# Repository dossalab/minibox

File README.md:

## Minibox

This is a small Bluetooth receiver for remote controlled toys or small models. Receiver has 5 hobby servo / ESC outputs.
Since Xbox One's controller is essentially a Bluetooth gamepad, it is possible to bridge two together, turning them into a complete remote control solution.

### Connection

Switch your receiver and gamepad on. The LED on the receiver should start blinking quickly, indicating that it is in scanning mode. Once it will discover the controller it will start connecting automatically. If the connection is successful LED will turn off - then you're ready to go!

### Some considerations

- Range & reliability is probably not that great. It should be alright for cars and other ground vehicles but flying a drone like that could be dangerous (although I did);
- In case of inactivity (user is not interacting with the controller / not moving sticks), servos have to be reset to their initial position. That's because Xbox controller is designed for gaming, not for remote control. Once you stop moving sticks, controller enters low-power mode and stops sending data. Same happens when your model gets out of reach. It is hard for the receiver to distinguish these scenarios, so it has to disarm outputs in both cases (otherwise your model is at risk of running away :)

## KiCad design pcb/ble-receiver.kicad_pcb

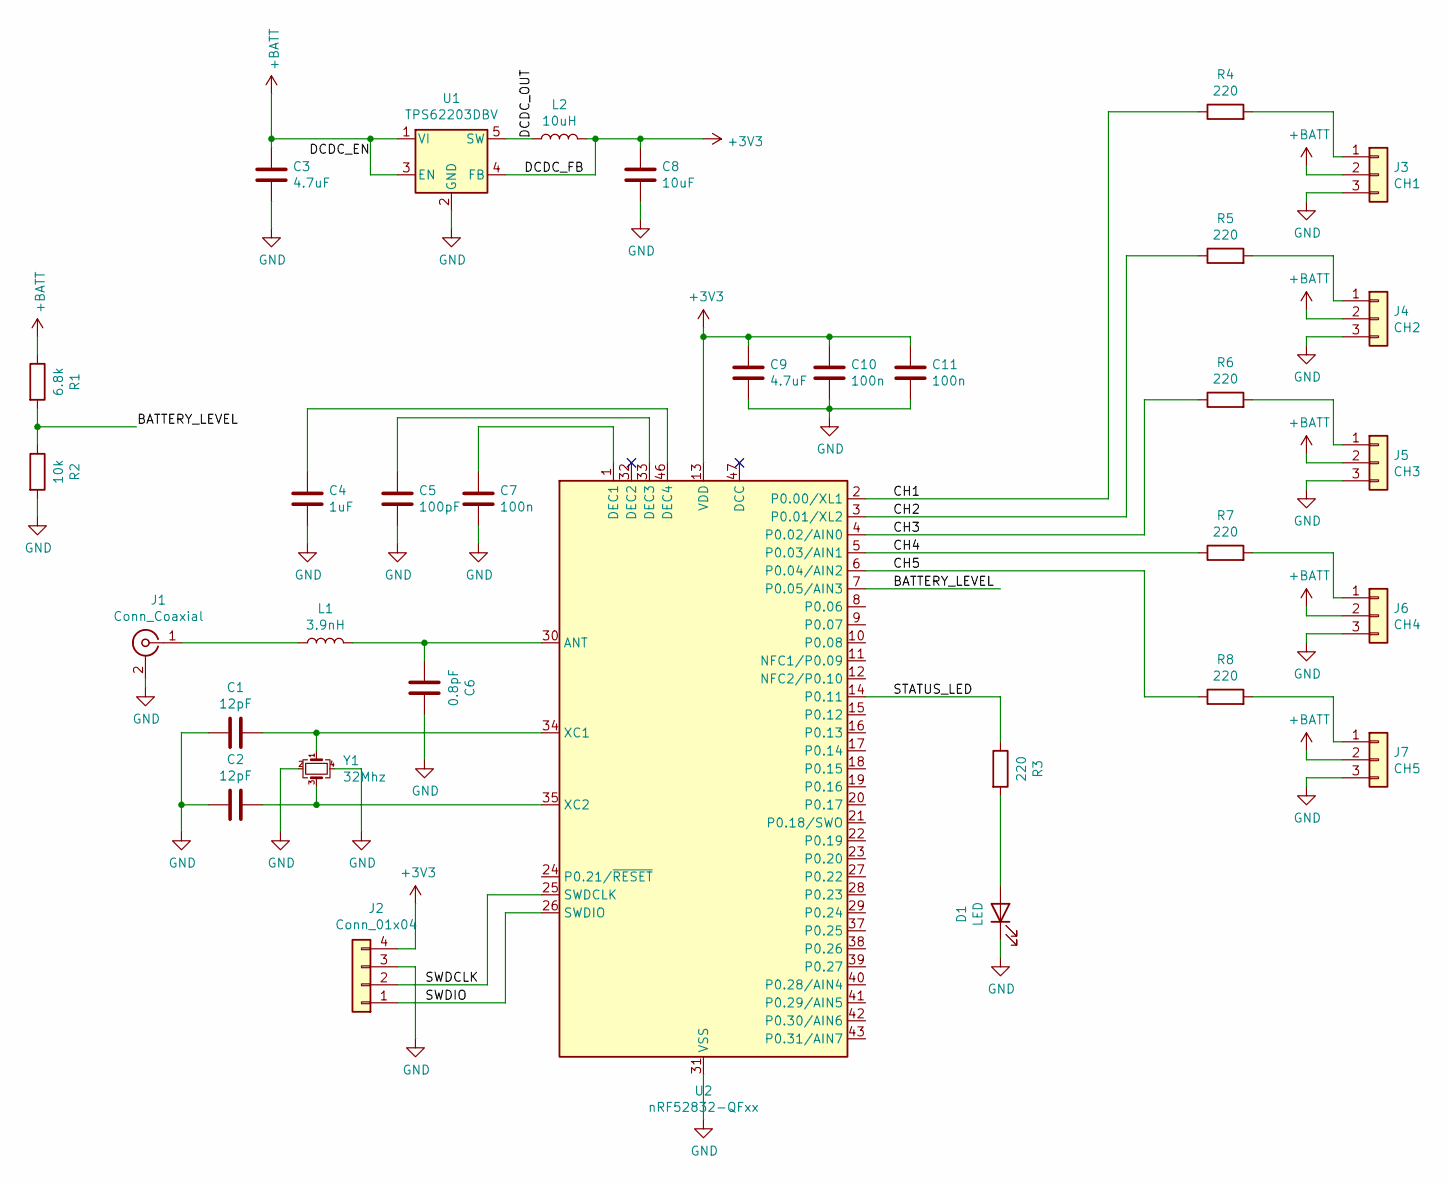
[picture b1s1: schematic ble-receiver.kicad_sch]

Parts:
C1, C2: 12pF; C_0603_1608Metric
C3, C9: 4.7uF; C_0603_1608Metric
C4: 1uF; C_0603_1608Metric
C5: 100pF; C_0603_1608Metric
C6: 0.8pF; C_0603_1608Metric
C7, C10, C11: 100n; C_0603_1608Metric
C8: 10uF; C_0603_1608Metric
D1: LED; LED_0603_1608Metric
J1: Conn_Coaxial; U.FL_Hirose_U.FL-R-SMT-1_Vertical
J2: Conn_01x04; PinHeader_1x04_P2.54mm_Vertical
J3: CH1; PinHeader_1x03_P2.54mm_Vertical
J4: CH2; PinHeader_1x03_P2.54mm_Vertical
J5: CH3; PinHeader_1x03_P2.54mm_Vertical
J6: CH4; PinHeader_1x03_P2.54mm_Vertical
J7: CH5; PinHeader_1x03_P2.54mm_Vertical
L1: 3.9nH; L_0603_1608Metric
L2: 10uH; L_0805_2012Metric
R1: 6.8k; R_0603_1608Metric
R2: 10k; R_0603_1608Metric
R3, R4, R5, R6, R7, R8: 220; R_0603_1608Metric
U1: TPS62203DBV; SOT-23-5
U2: nRF52832-QFxx; QFN-48-1EP_6x6mm_P0.4mm_EP4.6x4.6mm
Y1: 32Mhz; Crystal_SMD_2520-4Pin_2.5x2.0mm

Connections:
+3V3: C8.2, C9.2, C10.2, C11.2, J2.4, L2.2, U1.4 (FB), U2.13 (VDD), U2.36 (VDD), U2.48 (VDD)
+BATT: C3.2, J3.2, J4.2, J5.2, J6.2, J7.2, R1.1, U1.1 (VI), U1.3 (EN)
/BATTERY_LEVEL: R1.2, R2.1, U2.7 (P0.05/AIN3)
/CH1: R4.1, U2.2 (P0.00/XL1)
/CH2: R5.1, U2.3 (P0.01/XL2)
/CH3: R6.1, U2.4 (P0.02/AIN0)
/CH4: R7.1, U2.5 (P0.03/AIN1)
/CH5: R8.1, U2.6 (P0.04/AIN2)
/DCDC_OUT: L2.1, U1.5 (SW)
/STATUS_LED: R3.1, U2.14 (P0.11)
/SWDCLK: J2.2, U2.25 (SWDCLK)
/SWDIO: J2.1, U2.26 (SWDIO)
GND: C1.2, C2.2, C3.1, C4.1, C5.1, C6.1, C7.1, C8.1, C9.1, C10.1, C11.1, D1.1 (K), J1.2 (Ext), J2.3, J3.3, J4.3, J5.3, J6.3, J7.3, R2.2, U1.2 (GND), U2.31 (VSS), U2.45 (VSS), U2.49 (VSS), Y1.2, Y1.4
unnamed: D1.2 (A), R3.2
unnamed: J1.1 (In), L1.1
unnamed: J3.1, R4.2
unnamed: J4.1, R5.2
unnamed: J5.1, R6.2
unnamed: J6.1, R7.2
unnamed: J7.1, R8.2
unnamed: C6.2, L1.2, U2.30 (ANT)
unnamed: C7.2, U2.1 (DEC1)
unnamed: C5.2, U2.33 (DEC3)
unnamed: C4.2, U2.46 (DEC4)
unnamed: C1.1, U2.34 (XC1), Y1.1
unnamed: C2.1, U2.35 (XC2), Y1.3

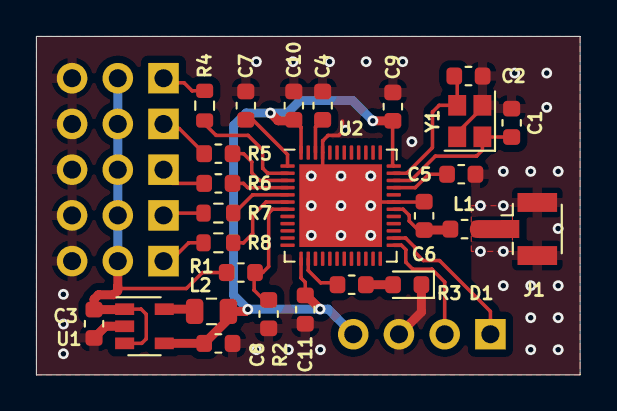
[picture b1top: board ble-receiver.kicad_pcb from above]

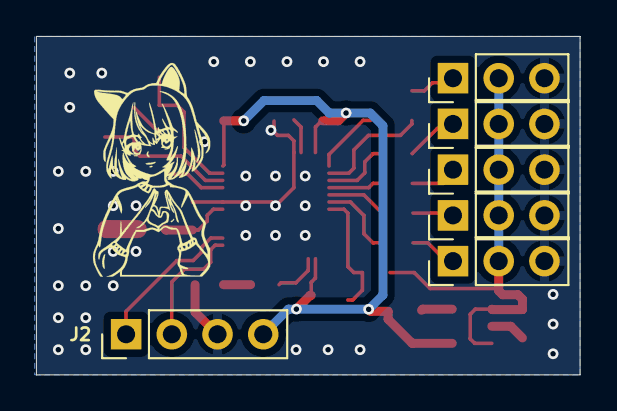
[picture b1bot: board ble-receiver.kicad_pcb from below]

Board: 2 copper layers, 30.2 x 18.8 mm, 32 parts (6 on the bottom side), 26 nets.

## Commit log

2024-03-21 init commit
2024-03-23 basic demo with motors & stuff
2024-07-07 stabilize
2024-07-10 switch to reset the board
2025-07-25 capture
2025-07-26 scanning & connecting works (no data yet :()
2025-07-26 make joystick work :)
2025-07-26 bump embassy versions
2025-07-26 small cleanup
2025-07-26 try to make indications work
2025-07-26 new indications :)
2025-07-26 add PCB
2025-07-26 bump kicad version
2025-07-26 update readme and license
